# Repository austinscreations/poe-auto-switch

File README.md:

# poe-auto-switch
a circuit designed to handle all 3 forms of poe and auto switch between them as required

802.3af POE aka auto negotated with a network switch (pins 1/2 &3/6) 
802.3af Passive POE (pins 4/5 & 7/8)
DIY POE (pins 4/5 & 7/8)

see it in action on youtube: 

https://www.youtube.com/watch?v=DrwicD6_NDw

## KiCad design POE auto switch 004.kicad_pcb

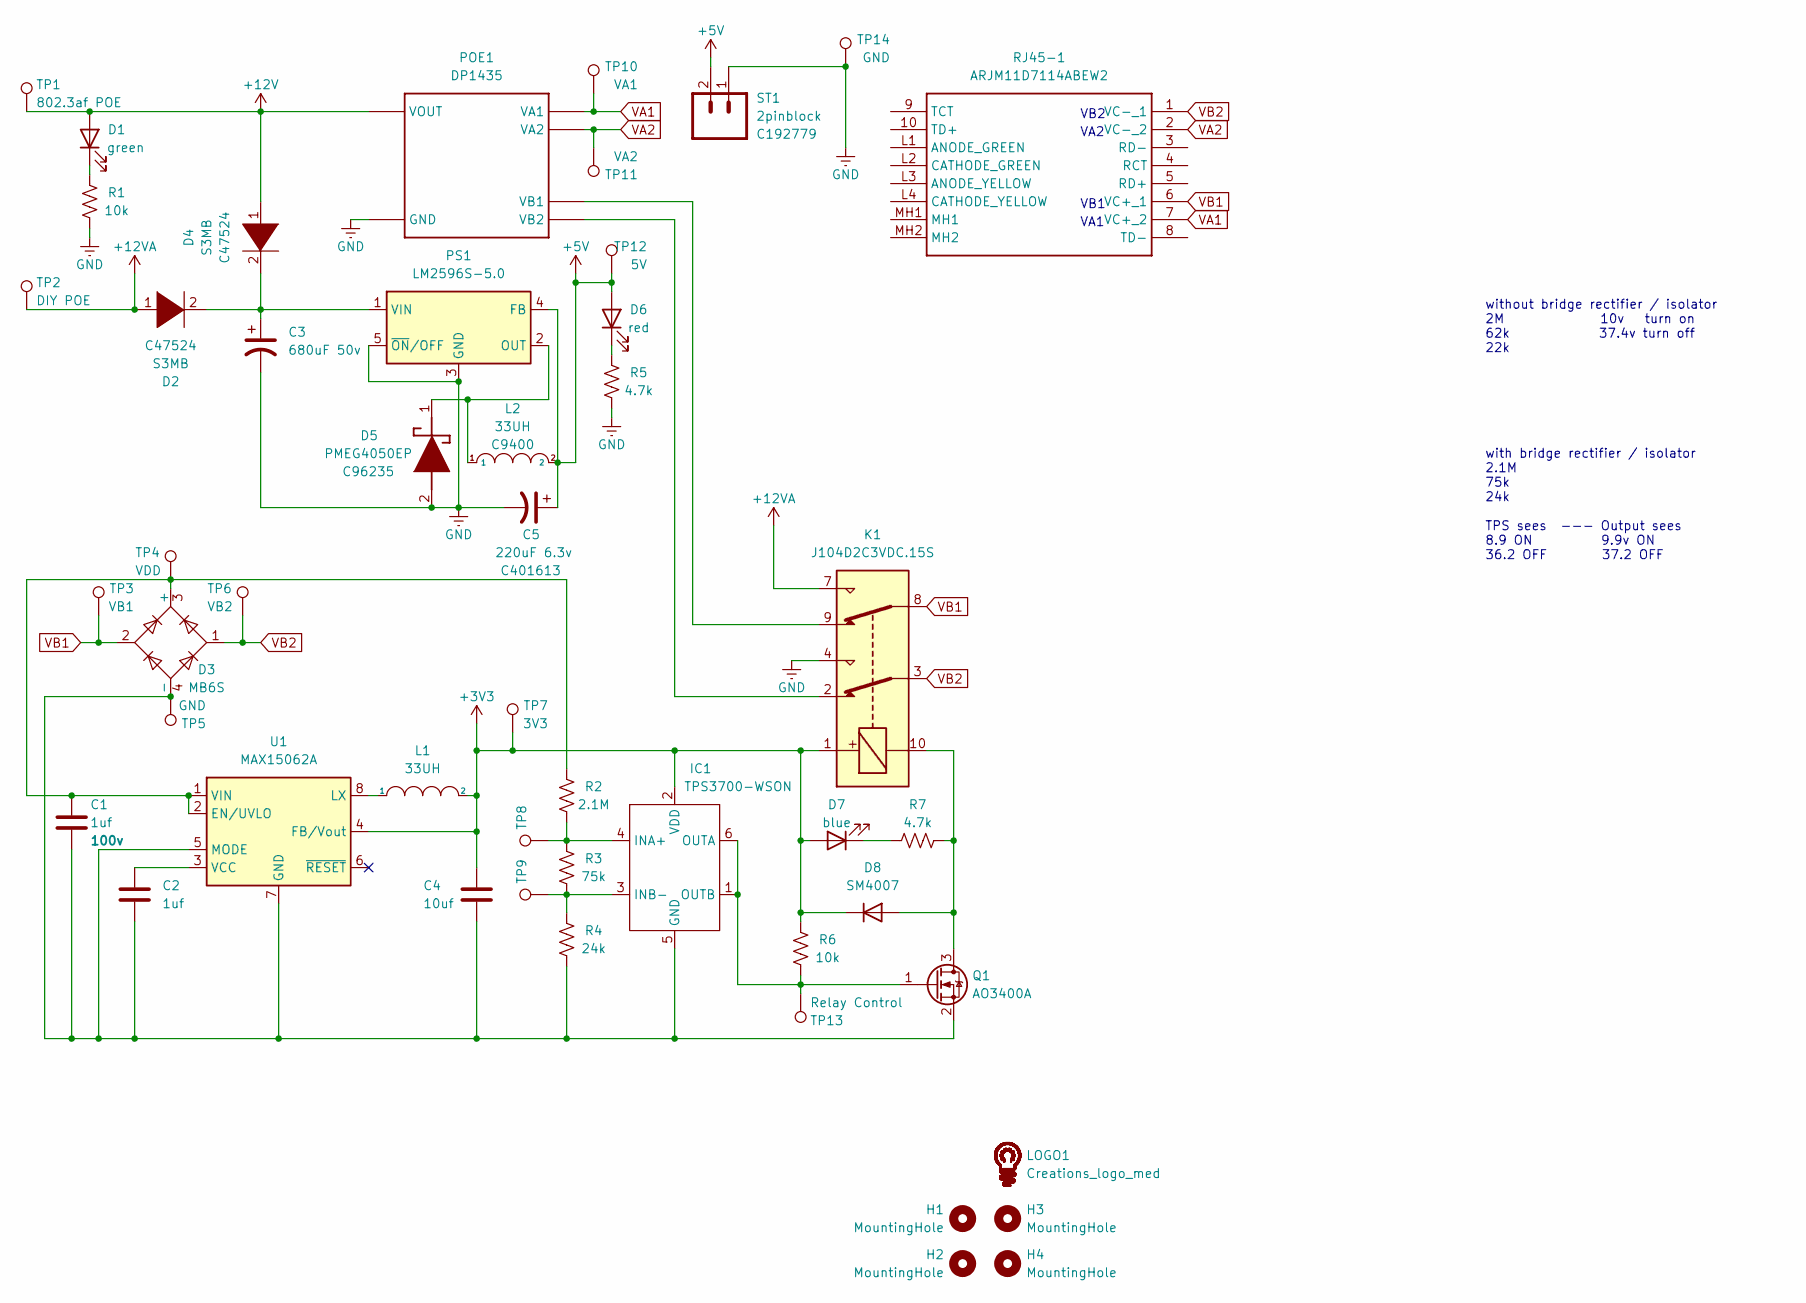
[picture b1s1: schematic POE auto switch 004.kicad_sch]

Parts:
C1: 1uf; C_0805_2012Metric; voltage 100v
C2: 1uf; C_0603_1608Metric
C3: 680uF 50v; CP_Radial_D13.0mm_P5.00mm
C4: 10uf; C_0603_1608Metric
C5: 220uF 6.3v; CP_Elec_8x6.2; part # C401613
D1: green; LED_0603_1608Metric
D2, D4: S3MB; D_SMB; part # C47524
D3: MB6S; TO-269AA
D5: PMEG4050EP; PMEG3050EP; part # C96235
D6: red; LED_0603_1608Metric
D7: blue; LED_0603_1608Metric
D8: SM4007; D_SOD-123F
H1, H2, H3, H4: MountingHole; MountingHole_3.2mm_M3
IC1: TPS3700-WSON; WSON-6_1.5x1.5mm_P0.5mm
K1: J104D2C3VDC.15S; Relay_DPDT_Finder_30.22
L1: 33UH; L_Vishay_IFSC-1515AH_4x4x1.8mm
L2: 33UH; 12x12x8 inductor; part # C9400
LOGO1: Creations_logo_med; Creations logo med
POE1: DP1435
PS1: LM2596S-5.0; LM2596S
Q1: AO3400A; SOT-23
R1, R6: 10k; R_0603_1608Metric
R2: 2.1M; R_0603_1608Metric
R3: 75k; R_0603_1608Metric
R4: 24k; R_0603_1608Metric
R5, R7: 4.7k; R_0603_1608Metric
RJ45-1: ARJM11D7114ABEW2
ST1: 2pinblock; part # C192779
TP1: 802.3af POE; TestPoint_Pad_D2.0mm
TP2: DIY POE; TestPoint_Pad_D2.0mm
TP3: VB1; TestPoint_Pad_D2.0mm
TP4: VDD; TestPoint_Pad_D2.0mm
TP5, TP14: GND; TestPoint_Pad_D2.0mm
TP6: VB2; TestPoint_Pad_D2.0mm
TP7: 3V3; TestPoint_Pad_D2.0mm
TP8, TP9: testpoint; TestPoint_Pad_D2.0mm
TP10: VA1; TestPoint_Pad_D2.0mm
TP11: VA2; TestPoint_Pad_D2.0mm
TP12: 5V; TestPoint_Pad_D2.0mm
TP13: Relay Control; TestPoint_Pad_D2.0mm
U1: MAX15062A; DFN-8_2x2mm_P0.5mm

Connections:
+3V3: C4.1, D7.2 (A), D8.1 (K), IC1.2 (VDD), K1.1, L1.2, R6.1, TP7.1, U1.4 (FB/Vout)
+5V: C5.1, D6.2 (A), L2.2, PS1.4 (FB), ST1.2, TP12.1
+12V: D1.2 (A), D4.1 (K), POE1.VOUT, TP1.1
+12VA: D2.1 (K), K1.7, TP2.1
GNDREF: C3.2, C5.2, D5.2 (A), K1.4, POE1.GND, PS1.3 (GND), PS1.5 (~ON/OFF), R1.2, R5.2, ST1.1, TP14.1
unnamed: C1.1, D3.3 (+), R2.1, TP4.1, U1.1 (VIN), U1.2 (EN/UVLO)
unnamed: C1.2, C2.2, C4.2, D3.4 (-), IC1.5 (GND), Q1.2 (S), R4.2, TP5.1, U1.5 (MODE), U1.7 (GND)
unnamed: C2.1, U1.3 (VCC)
unnamed: C3.1, D2.2 (A), D4.2 (A), PS1.1 (VIN)
unnamed: D1.1 (K), R1.1
unnamed: D5.1 (K), L2.1, PS1.2 (OUT)
unnamed: D6.1 (K), R5.1
unnamed: D7.1 (K), R7.1
unnamed: D8.2 (A), K1.10, Q1.3 (D), R7.2
unnamed: IC1.1 (OUTB), IC1.6 (OUTA), Q1.1 (G), R6.2, TP13.1
unnamed: IC1.3 (INB-), R3.2, R4.1, TP9.1
unnamed: IC1.4 (INA+), R2.2, R3.1, TP8.1
unnamed: K1.2, POE1.VB2
unnamed: K1.9, POE1.VB1
unnamed: L1.1, U1.8 (LX)
VA1: POE1.VA1, RJ45-1.7 (VC+_2), TP10.1
VA2: POE1.VA2, RJ45-1.2 (VC-_2), TP11.1
VB1: D3.2, K1.8, RJ45-1.6 (VC+_1), TP3.1
VB2: D3.1, K1.3, RJ45-1.1 (VC-_1), TP6.1

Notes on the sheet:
with bridge rectifier / isolator 2.1M 75k 24k TPS sees --- Output sees 8.9 ON 9.9v ON 36.2 OFF 37.2 OFF
without bridge rectifier / isolator 2M 10v turn on 62k 37.4v turn off 22k
VA1
VA2
VB2
VB1

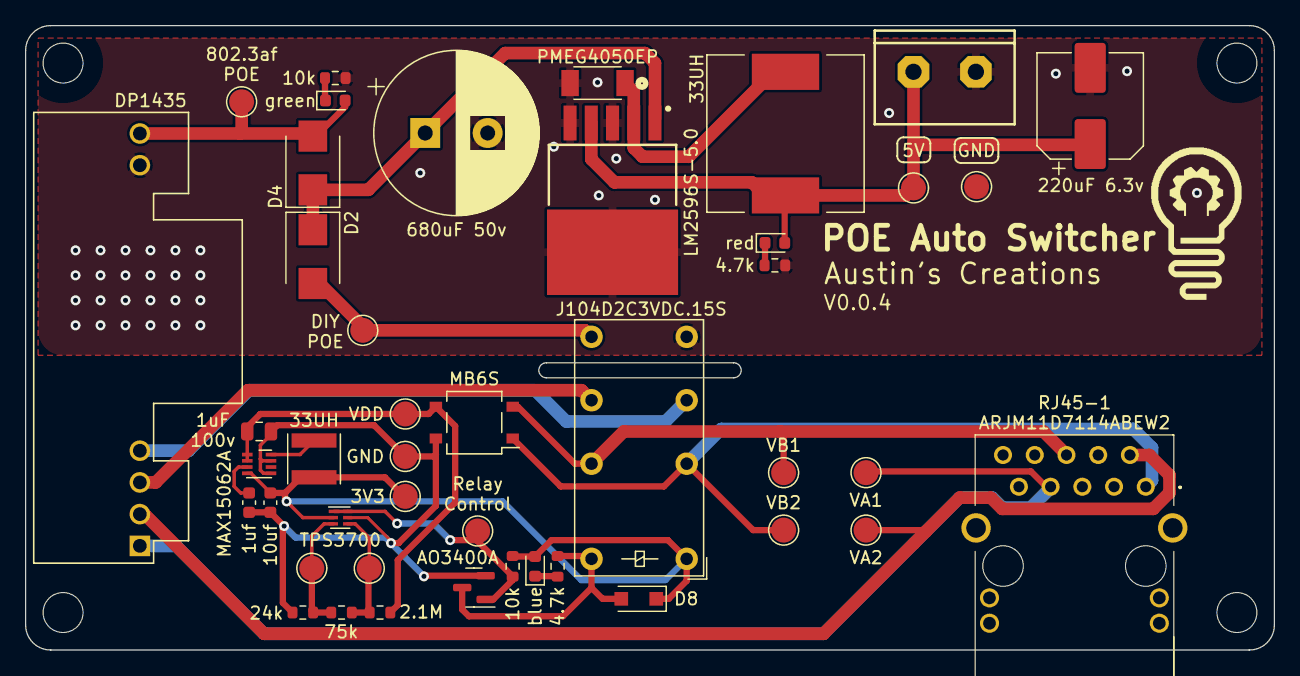
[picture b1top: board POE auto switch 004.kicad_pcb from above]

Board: 2 copper layers, 100.0 x 50.0 mm, 49 parts (0 on the bottom side), 24 nets.
